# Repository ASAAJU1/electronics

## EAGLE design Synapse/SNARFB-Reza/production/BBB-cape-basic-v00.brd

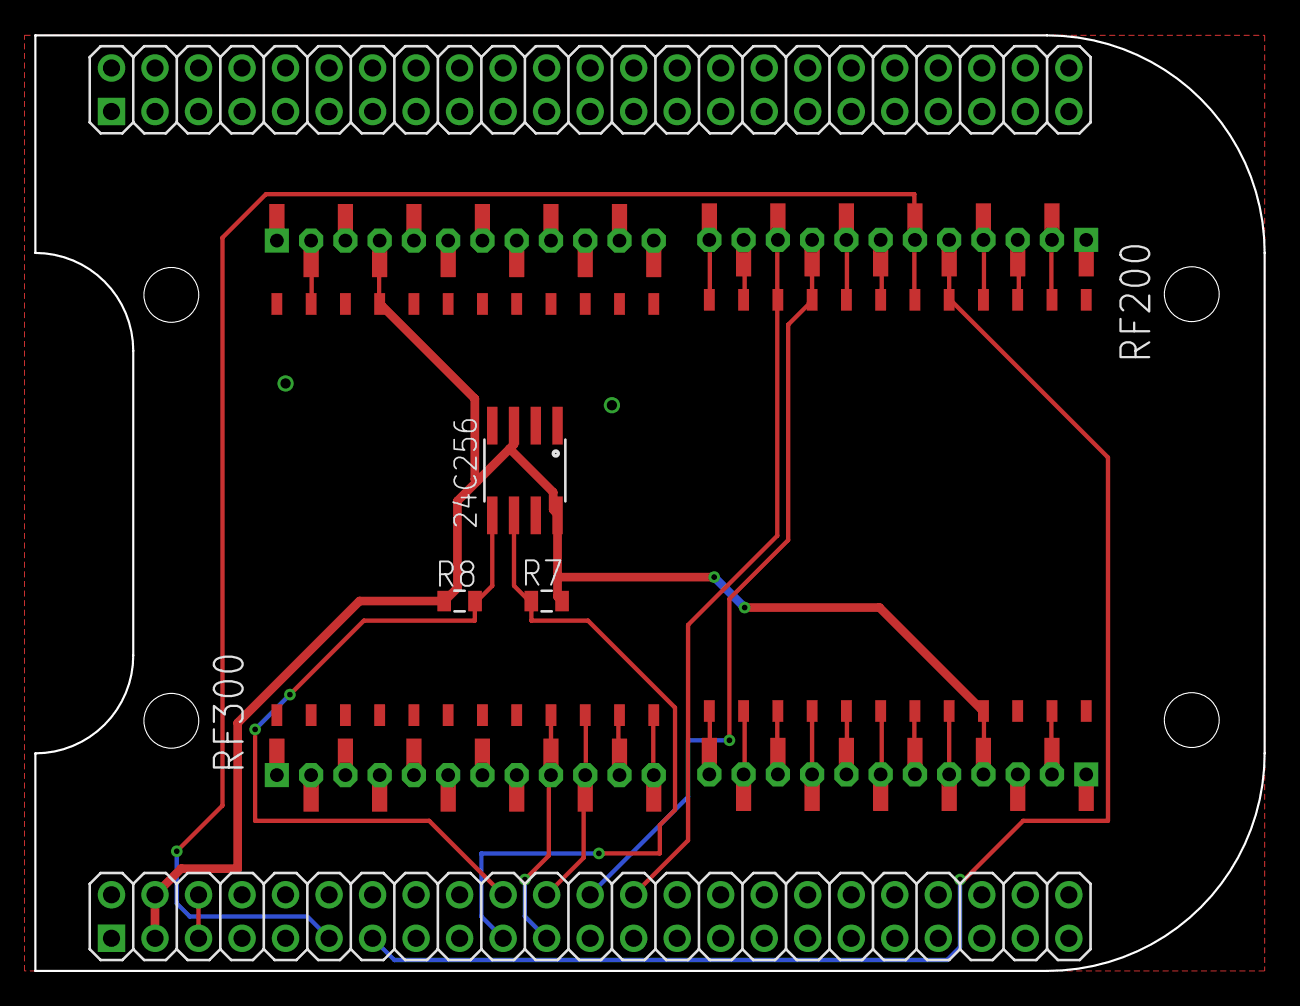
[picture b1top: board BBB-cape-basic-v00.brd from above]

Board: 2 copper layers, 71.8 x 54.6 mm, 6 parts (0 on the bottom side), 30 nets.

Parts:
24C256: EEPROM-I2CSMD; SO08
R7, R8: 5.6k,5%; 0805
RF200: rf200; SYNAPSERFENGINE-THM-SMT-JACK2
RF300: rf300; SYNAPSERFENGINE-THM-SMT-JACK2
U$1: BEAGLEBONE_OUTLINE; BEAGLEBONE_SHIELD

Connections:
GND: 24C256.1, 24C256.2, 24C256.4, RF200.1, RF200.24, RF200.P1, RF200.P24, RF200.P201, RF200.P224, RF300.1, RF300.24, RF300.P1, RF300.P24, RF300.P201, RF300.P224, U$1.1, U$1.2, U$1.47, U$1.48, U$1.89, U$1.90, U$1.91, U$1.92
I2C2_SCL: 24C256.6, R7.1, U$1.65
I2C2_SDA: 24C256.5, R8.1, U$1.66
unnamed: RF200.2, RF200.P2, RF200.P202
unnamed: RF200.3, RF200.P3, RF200.P203
unnamed: RF200.4, RF200.P4, RF200.P204
unnamed: RF200.7, RF200.P7, RF200.P207
unnamed: RF200.8, RF200.P8, RF200.P208
unnamed: RF300.11, RF300.P11, RF300.P211
unnamed: RF300.12, RF300.P12, RF300.P212
unnamed: RF200.11, RF200.P11, RF200.P211
unnamed: RF200.12, RF200.P12, RF200.P212
unnamed: RF200.23, RF200.P23, RF200.P223
unnamed: RF200.20, RF200.P20, RF200.P220
unnamed: RF200.19, RF200.P19, RF200.P219
unnamed: RF200.18, RF200.P18, RF200.P218
unnamed: RF200.17, RF200.P17, RF200.P217
unnamed: RF200.16, RF200.P16, RF200.P216
unnamed: RF200.15, RF200.P15, RF200.P215
unnamed: RF200.14, RF200.P14, RF200.P214
unnamed: RF200.13, RF200.P13, RF200.P213
unnamed: RF300.23, RF300.P23, RF300.P223
U1RX: RF200.10, RF200.P10, RF200.P210, U$1.72
U1TX: RF200.9, RF200.P9, RF200.P209, U$1.70
U2RX: RF300.10, RF300.P10, RF300.P210, U$1.68
U2TX: RF300.9, RF300.P9, RF300.P209, U$1.67
U4RX: RF200.6, RF200.P6, RF200.P206, U$1.57
U4TX: RF200.5, RF200.P5, RF200.P205, U$1.59
VCC3: 24C256.3, 24C256.8, R7.2, R8.2, RF200.21, RF200.P21, RF200.P221, RF300.21, RF300.P21, RF300.P221, U$1.49, U$1.50
VDD_5V: U$1.51, U$1.52

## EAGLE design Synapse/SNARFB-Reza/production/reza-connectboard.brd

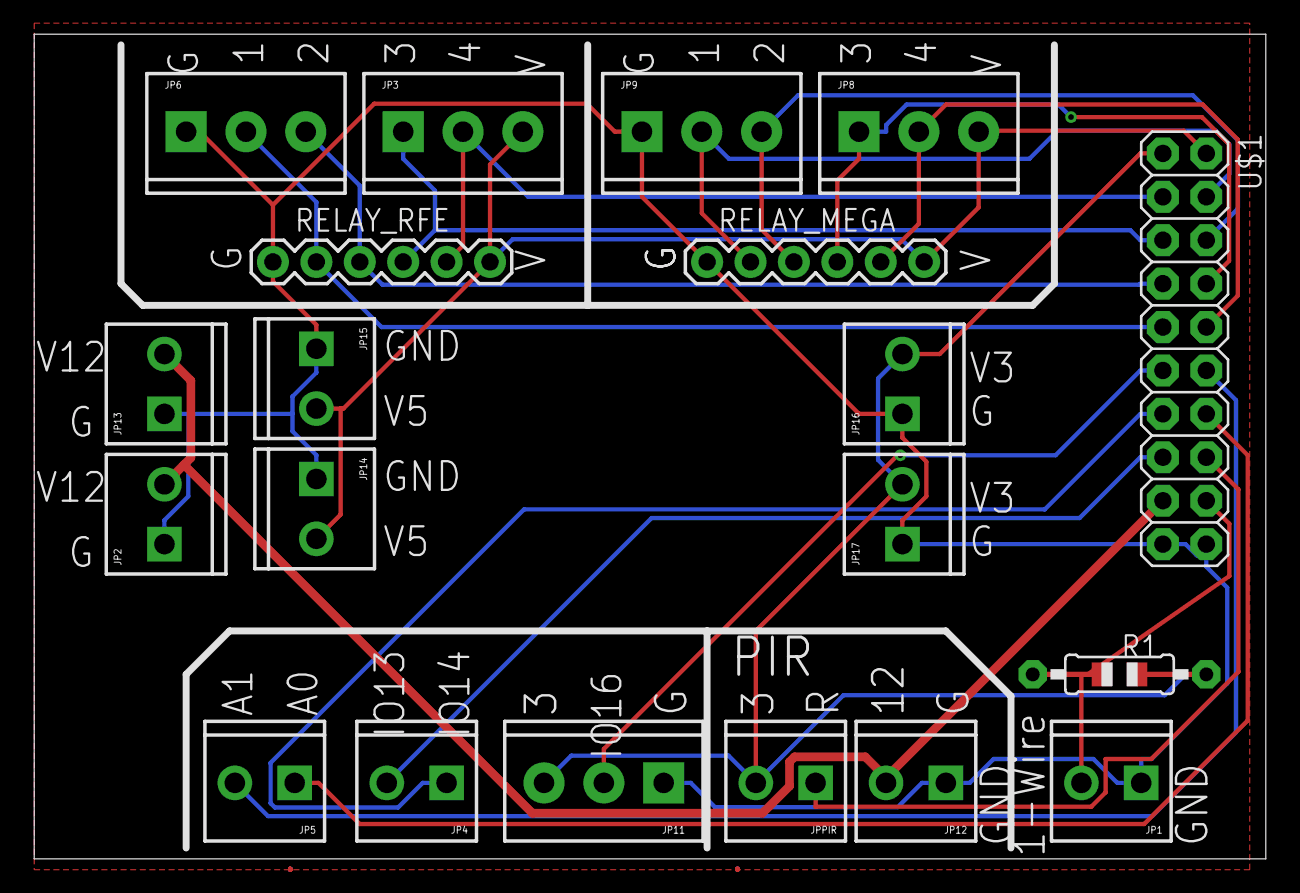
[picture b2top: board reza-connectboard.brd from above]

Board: 2 copper layers, 72.1 x 48.2 mm, 21 parts (0 on the bottom side), 19 nets.

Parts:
JP1, JP2, JP4, JP5, JP12, JP13, JP14, JP15, JP16, JP17: M023.5MM; SCREWTERMINAL-3.5MM-2
JP3, JP6, JP8, JP9, JP11: SCREWTERMINAL-3.5MM-3
JPPIR: M023.5MM; SCREWTERMINAL-3.5MM-2
R1: 0805-THM
RELAY_MEGA: 1X06
RELAY_RFE: 1X06
U$1: M10X2; 2X10
U$2: ENVIOSYS_LOGO2

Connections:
GND: JP1.1, JP2.1, JP6.1, JP9.1, JP11.1, JP12.1, JP13.1, JP14.1, JP15.1, JP16.1, JP17.1, RELAY_MEGA.1, RELAY_RFE.1, U$1.19, U$1.20
GPIO2: JP3.2, RELAY_RFE.5, U$1.3
GPIO5: JP3.1, RELAY_RFE.4, U$1.5
GPIO6: JP6.3, RELAY_RFE.3, U$1.7
GPIO13: JP4.2, U$1.15
GPIO14: JP4.1, U$1.13
GPIO15: JP6.2, RELAY_RFE.2, U$1.9
GPIO16: JP11.2, U$1.11
PC6-D5: JPPIR.1, U$1.16
PD7-D6: JP1.2, R1.2, U$1.18
PF0-A5: JP9.2, RELAY_MEGA.2, U$1.4
PF1-A4: JP9.3, RELAY_MEGA.3, U$1.6
PF4-A3: JP8.1, RELAY_MEGA.4, U$1.8
PF5-A2: JP8.2, RELAY_MEGA.5, U$1.10
PF6-A1: JP5.2, U$1.12
PF7-A0: JP5.1, U$1.14
VCC3: JP11.3, JP16.2, JP17.2, JPPIR.2, R1.1, U$1.1
VCC5: JP3.3, JP8.3, JP14.2, JP15.2, RELAY_MEGA.6, RELAY_RFE.6, U$1.2
VCC12: JP2.2, JP12.2, JP13.2, U$1.17

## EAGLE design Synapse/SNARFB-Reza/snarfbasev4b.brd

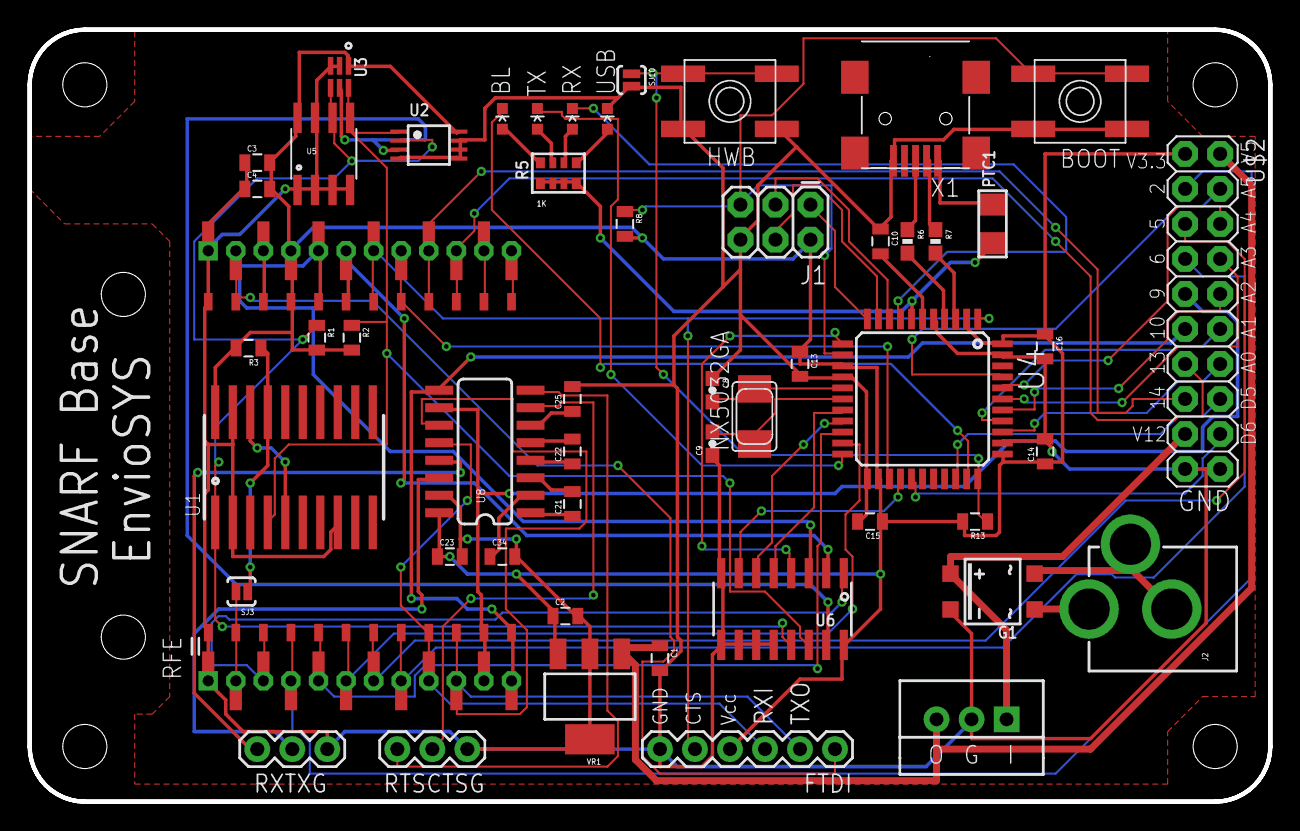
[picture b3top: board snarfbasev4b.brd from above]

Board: 2 copper layers, 90.0 x 56.0 mm, 54 parts (1 on the bottom side), 75 nets.

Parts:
BL: RED; LED-0603
BOOT: EVQQ2; EVQ-Q2
C1, C2, C3, C10, C13, C14, C15, C16: 1uF; 0805
C4: 10uF; 0805
C8, C9: 12pF; 0603-CAP
C21, C22, C23, C25, C34: 0.1uF; 0805
FTDI: 1X06
G1: SOIC-4
HWB: EVQQ2; EVQ-Q2
IC1: TO220-MURATA
J1: AVR_SPI_PRG_6PTH; 2X3
J2: POWER_JACKPTH; POWER_JACK_PTH
NX5032GA: 8MHz; NX5032
PTC1: 1206
R1, R2: 0805
R3: 10k; 0805
R5: 1K; RESPACK_4X0603
R6, R7: 22; 0603-RES
R8, R13: 10K; 0805
RFE: RFE; SYNAPSERFENGINE-THM-SMT-JACK2
RTSCTSG: 1X03
RX: yellow; LED-0603
RXTXG: RX TX G; 1X03
SJ3: SOLDERJUMPERNC2; SJ_2S-NOTRACE
SJ10: HWB; SJ_2S-NO
TX: yellow; LED-0603
U1: PCF2129ASO20; SO20W
U2: lm75adp; TSSOP8
U3: TSL2561_DFN; TSL2561_FN
U4: ATMEGA32U4-AU; TQFP44
U5: 24LC256T-I/SN; SO08
U6: PCA9541SO16-2; SOIC16
U8: MAX3232EIDWR; SO016
U$1: ENVIOSYS_LOGO2
U$2: M10X2; 2X10
U$3: DP9056_V1
USB: GREEN; LED-0603
VR1: MCP1826S; SOT223
X1: USBSMD; USB-MINIB

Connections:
!TLINT: U2.3, U3.INT, U6.15
ARXLED: RX.C, U4.8
ATXLED: TX.C, U4.22
CTS1: RTSCTSG.2, U8.7
GND: BOOT.B, BOOT.B', C1.2, C2.2, C3.1, C4.1, C8.1, C9.1, C10.1, C13.2, C14.2, C15.2, C16.2, C23.2, C25.2, C34.2, FTDI.6, G1.-, HWB.B, HWB.B', IC1.GND, J1.6, RFE.1, RFE.24, RFE.P1, RFE.P24, RFE.P201, RFE.P224, RTSCTSG.1, RXTXG.1, SJ10.2, U1.P$2, U1.P$8, U1.P$19, U2.4, U2.5, U2.6, U2.7, U3.ADR, U3.VSS, U4.5, U4.15, U4.23, U4.35, U4.43, U5.1, U5.2, U5.3, U5.4, U5.7, U6.8, U6.9, U6.10, U6.11, U6.12, U8.15, U$2.19, U$2.20, USB.C, VR1.2, VR1.4, X1.GND
GPIO0_RTCINT: RFE.2, RFE.P2, RFE.P202, SJ3.2
GPIO1_I2CINT: RFE.3, RFE.P3, RFE.P203, U6.1
GPIO2_PINHD: RFE.4, RFE.P4, RFE.P204, U$2.3
GPIO5_PINHD: RFE.7, RFE.P7, RFE.P207, U$2.5
GPIO6_PINHD: RFE.8, RFE.P8, RFE.P208, U$2.7
GPIO9_PINHD: RFE.11, RFE.P11, RFE.P211, U8.10, U$2.9
GPIO10_PINHD: RFE.12, RFE.P12, RFE.P212, U8.9, U$2.11
GPIO11: RFE.13, RFE.P13, RFE.P213
GPIO12: RFE.14, RFE.P14, RFE.P214
GPIO13_PINHD: RFE.15, RFE.P15, RFE.P215, U$2.13
GPIO14_PINHD: RFE.16, RFE.P16, RFE.P216, U$2.15
GPIO19: RFE.22, RFE.P22, RFE.P222
HWB: HWB.A, HWB.A', R13.1, SJ10.1, U4.33
IFS: U1.P$5, U1.P$18
MISO: J1.1, U4.11
MOSI: J1.4, U4.10
unnamed: G1.~1, J2.PWR
unnamed: C10.2, U4.6
unnamed: BL.A, R5.8
unnamed: G1.~2, J2.GND, J2.GNDBREAK
unnamed: R5.7, TX.A
unnamed: R5.6, RX.A
unnamed: R5.5, USB.A
unnamed: C21.2, U8.3
unnamed: C22.2, U8.5
unnamed: C34.1, U8.2
unnamed: C25.1, U8.6
unnamed: C21.1, U8.1
unnamed: C22.1, U8.4
PB7-D11-I2CRST: U4.12, U6.4
PC6-D5: U4.31, U$2.16
PC7-D13-LEDBL: BL.C, U4.32
PD4-D4-GPIO15: RFE.17, RFE.P17, RFE.P217, U4.25
PD6-D12-I2C: U4.26, U6.7
PD7-D6: U4.27, U$2.18
PE6-D7-GPIO16: FTDI.5, RFE.18, RFE.P18, RFE.P218, U4.1
PF0-A5: U4.41, U$2.4
PF1-A4: U4.40, U$2.6
PF4-A3: U4.39, U$2.8
PF5-A2: U4.38, U$2.10
PF6-A1: U4.37, U$2.12
PF7-A0: U4.36, U$2.14
R6: R3.1, SJ3.1, U1.P$17
RESET_L: FTDI.1, RFE.23, RFE.P23, RFE.P223
RST: BOOT.A, BOOT.A', J1.5, R8.1, U4.13
RTS1: RTSCTSG.3, U8.8
RX0: RXTXG.3, U8.13
RX1: RFE.6, RFE.P6, RFE.P206, U4.21
RXI: FTDI.3, RFE.9, RFE.P9, RFE.P209, U8.12
SCK: J1.3, U4.9
SCL0: RFE.20, RFE.P20, RFE.P220, U6.3
SCL1: U4.18, U6.5
SCL3: R1.1, U1.P$1, U2.2, U3.CLK, U5.6, U6.13
SDA0: RFE.19, RFE.P19, RFE.P219, U6.2
SDA1: U4.19, U6.6
SDA3: R2.1, U1.P$4, U2.1, U3.DATA, U5.5, U6.14
TX0: RXTXG.2, U8.14
TX1: RFE.5, RFE.P5, RFE.P205, U4.20
TXO: FTDI.2, RFE.10, RFE.P10, RFE.P210, U8.11
UDM_N: R7.1, X1.D-
UDM_P: R6.1, X1.D+
UD_N: R7.2, U4.3
UD_P: R6.2, U4.4
VBUS: PTC1.1, R5.1, R5.2, R5.3, R5.4, U4.7
VBUSRAW: PTC1.2, X1.VBUS
VCC3: C2.1, C3.2, C4.2, C13.1, C14.1, C15.1, C16.1, C23.1, FTDI.4, J1.2, R1.2, R2.2, R3.2, R8.2, R13.2, RFE.21, RFE.P21, RFE.P221, U1.P$20, U2.8, U3.VDD, U4.2, U4.14, U4.24, U4.34, U4.44, U5.8, U6.16, U8.16, U$2.1, VR1.3
VCC5: C1.1, IC1.OUT, U$2.2, VR1.1
VCC12: G1.+, IC1.IN, U$2.17
XTAL_N: C9.2, NX5032GA.P$2, U4.17
XTAL_P: C8.2, NX5032GA.P$1, U4.16

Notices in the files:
Synapse/SNARFB-Reza/snarfbasev4b.brd:
(c) Copyright 2013-2014 J.C. Woltz
parts and their libraries:
0_jc-custom-eagle6: CC BY-SA 3.0
SparkFun-Resistors: Licensing: CC v3.0 Share-Alike You are welcome to use this library for commercial purposes.
microbuilder: This work is placed in the public domain, and may be freely used for commercial and non-commercial work with the following conditions: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
